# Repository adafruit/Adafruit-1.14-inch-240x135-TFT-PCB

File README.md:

## Adafruit 1.14" 240x135 Color TFT Display + MicroSD Card Breakout - ST7789 PCB

<a href="http://www.adafruit.com/products/4383"><br/>
Click here to purchase one from the Adafruit shop</a>

PCB files for the Adafruit 1.14" 240x135 Color TFT Display + MicroSD Card Breakout - ST7789. 

Format is EagleCAD schematic and board layout
* https://www.adafruit.com/product/4383

### Description

Say hello to our 1.14" 240x135 Color TFT Display w/ MicroSD Card Breakout – we think it's T-F-Terrific! It's the size of your thumbnail, with glorious 240x135 high res pixel color. This very very small display is only 1.14" diagonal, packed with RGB pixels, for making very small high-density displays.

We've been looking for a display like this for a long time - it's so small only 1.14" diagonal but has a high density 260 ppi, 240x135 pixel display with full-angle viewing. It looks a lot like our 0.96" 160x80 display, but has 2.5x as many pixels. We've seen displays of this caliber used in smartwatches and small electronic devices but they've always been MIPI interface. Finally, we found one that is SPI and has a friendly display driver, so it works with any and all microcontrollers or microcomputers!

This lovely little display breakout is the best way to add a small, colorful and very bright display to any project. Since the display uses 4-wire SPI to communicate and has its own pixel-addressable frame buffer, it can be used with every kind of microcontroller. Even a very small one with low memory and few pins available! The 1.14" display has 240x135 16-bit full color pixels and is an IPS display, so the color looks great up to 80 degrees off axis in any direction. The TFT driver (ST7789) is very similar to the popular ST7735, and our Arduino library supports it well.

Our breakout has the TFT display soldered on (it uses a delicate flex-circuit connector) as well as a ultra-low-dropout 3.3V regulator and a 3/5V level shifter so you can use it with 3.3V or 5V power and logic. We also had a little space so we placed a microSD card holder so you can easily load full color bitmaps from a FAT16/FAT32 formatted microSD card. The microSD card is not included, [but you can pick one up here](http://www.adafruit.com/products/102).

Of course, we wouldn't just leave you with a datasheet and a "good luck!" - [we've written a full open source graphics library that can draw pixels, lines, rectangles, circles, text and bitmaps as well as example code and a wiring tutorial](https://learn.adafruit.com/adafruit-1-3-and-1-54-240-x-240-wide-angle-tft-lcd-displays/circuitpython-displayio-quickstart). The code is written for Arduino IDE but can be easily ported to your favorite microcontroller!

### License

Adafruit invests time and resources providing this open source design, please support Adafruit and open-source hardware by purchasing products from [Adafruit](https://www.adafruit.com)!

Designed by Limor Fried/Ladyada for Adafruit Industries.

Creative Commons Attribution/Share-Alike, all text above must be included in any redistribution. 
See license.txt for additional details.

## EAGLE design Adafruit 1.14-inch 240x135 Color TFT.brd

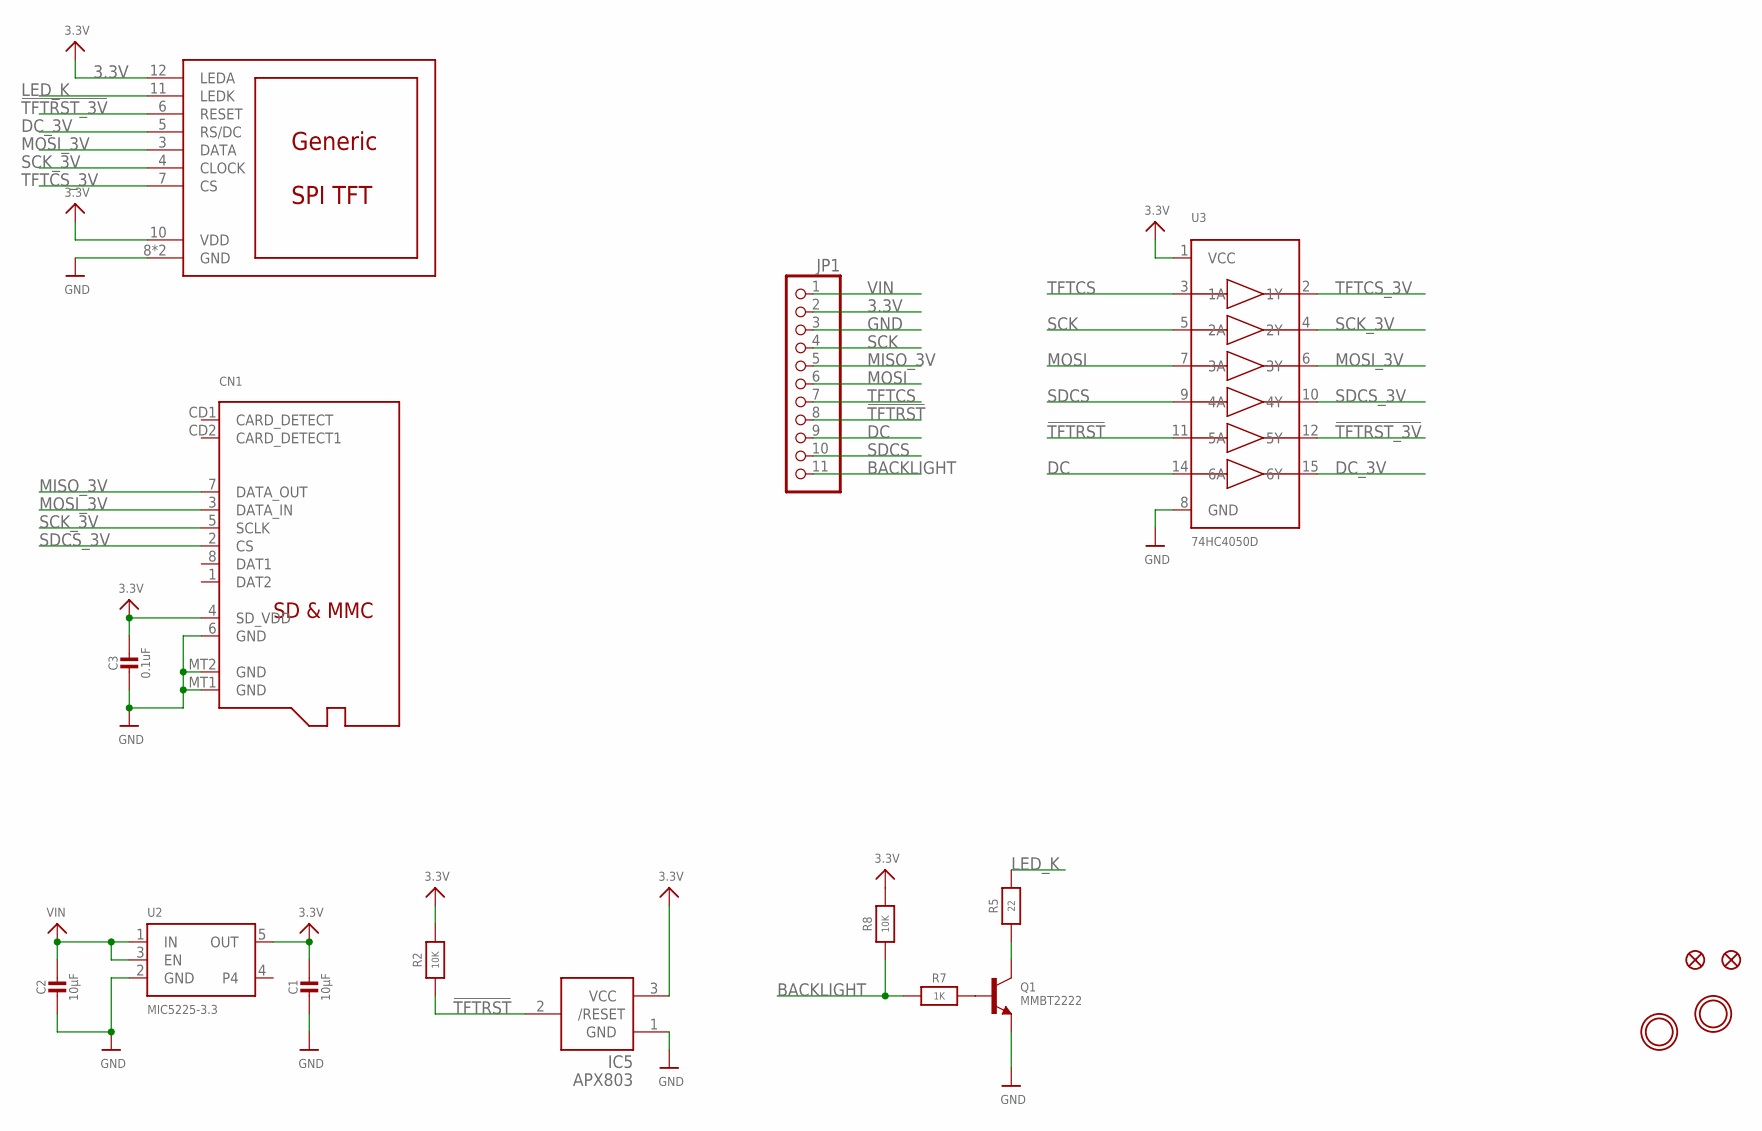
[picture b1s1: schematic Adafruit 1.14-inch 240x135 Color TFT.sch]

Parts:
C1, C2: 10µF; 0805-NO
C3: 0.1uF; 0805-NO
CN1: MICROSD
DISP1: DISP_LCD_GENERIC_SPI_1.14IN_240X135_WRAPUNDER; TFT_1.14IN_240X135_WRAPUNDER
FID1, FID2: FIDUCIAL_1MM
IC5: APX803; SOT23
JP1: HEADER-1X11; 1X11_ROUND
Q1: MMBT2222; SOT23-WIDE
R2, R8: 10K; 0603-NO
R5: 22; 0603-NO
R7: 1K; 0603-NO
U2: MIC5225-3.3; SOT23-5
U3: 74HC4050D; SOIC16
U$9, U$10: MOUNTINGHOLE2.5; MOUNTINGHOLE_2.5_PLATED

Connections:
3.3V: C1.1, C3.1, CN1.4 (SD_VDD), DISP1.10 (VDD), DISP1.12 (LEDA), IC5.3 (VCC), JP1.2, R2.2, R8.2, U2.5 (OUT), U3.1 (VCC)
!TFTRST: IC5.2 (/RESET), JP1.8, R2.1, U3.11 (5A)
!TFTRST_3V: DISP1.6 (RESET), U3.12 (5Y)
BACKLIGHT: JP1.11, R7.1, R8.1
DC: JP1.9, U3.14 (6A)
DC_3V: DISP1.5 (RS/DC), U3.15 (6Y)
GND: C1.2, C2.2, C3.2, CN1.6 (GND), CN1.MT1 (GND), CN1.MT2 (GND), DISP1.8 (GND), DISP1.13 (GND), IC5.1 (GND), JP1.3, Q1.2 (E), U2.2 (GND), U3.8 (GND)
LED_K: DISP1.11 (LEDK), R5.2
MISO_3V: CN1.7 (DATA_OUT), JP1.5
MOSI: JP1.6, U3.7 (3A)
MOSI_3V: CN1.3 (DATA_IN), DISP1.3 (DATA), U3.6 (3Y)
unnamed: Q1.1 (B), R7.2
unnamed: Q1.3 (C), R5.1
SCK: JP1.4, U3.5 (2A)
SCK_3V: CN1.5 (SCLK), DISP1.4 (CLOCK), U3.4 (2Y)
SDCS: JP1.10, U3.9 (4A)
SDCS_3V: CN1.2 (CS), U3.10 (4Y)
TFTCS: JP1.7, U3.3 (1A)
TFTCS_3V: DISP1.7 (CS), U3.2 (1Y)
VIN: C2.1, JP1.1, U2.1 (IN), U2.3 (EN)

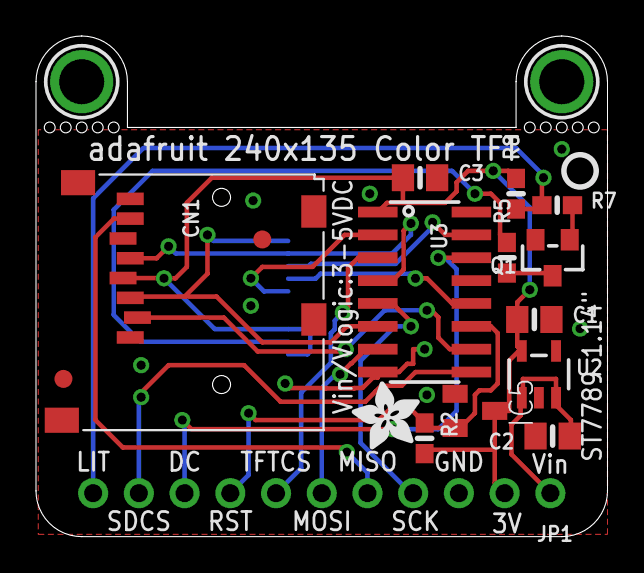
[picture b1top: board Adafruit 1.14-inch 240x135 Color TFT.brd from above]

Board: 2 copper layers, 31.8 x 27.8 mm, 20 parts (1 on the bottom side), 20 nets.

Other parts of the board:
U$4: MICROSD; ADAFRUIT_3.5MM
U$6: PCBFEAT-REV-040
